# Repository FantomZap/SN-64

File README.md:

# SN 64

SN 64 is an active engineering project for an FPGA-based SNES/Super Famicom cartridge adapter. **The target is one adapter for both an original Nintendo 64 and ModRetro M64 through the standard N64 cartridge interface, without internal console modifications.** Compatibility has not yet been demonstrated on hardware.

The FPGA will recreate the SNES motherboard environment and provide a protected, complete SNES cartridge interface. Original SNES/SFC cartridges, Super EverDrive X5/X6, and FXPAK Pro are primary compatibility targets. The host console supplies controller input and runs the adapter's configuration and diagnostics bootstrap.

## Current status

**The project now includes a simulated SNES console candidate with a contention-checked physical cartridge bridge and a simulated N64/M64 host endpoint (reused SummerCart64 PI controller with an SN64 ROM window and mailbox), editable mechanical reference parts, and the KiCad cartridge/USB circuit draft. No completed or tested SN 64 hardware exists yet.** The [core evaluation](fpga/README.md) reuses pinned SNESTang sources and includes original diagnostics, synthesis and internal FPGA fit experiments. The [mechanical package](mechanical/README.md) contains FreeCAD, STEP and STL files for a socket hole-pattern coupon and source N64 board reference; these are not a final enclosure. The [editable schematic](hardware/sn64/README.md), revision `0.4-r3`, contains both cartridge connectors and five child sheets wired together by a shared net-name contract: the [USB programmer](hardware/sn64/usb-programmer.kicad_sch) (USB-C, protection, FT232HL, isolated JTAG), the [cartridge interface](hardware/sn64/cart-interface.kicad_sch) (5 V/3.3 V translators, reset/IRQ/CIC), the [FPGA](hardware/sn64/fpga.kicad_sch) (ECP5-85F with every ball assigned, configuration flash, N64 bus switches), [power](hardware/sn64/power.kicad_sch) (host/USB source selection, regulators, default-off cartridge power, monitors) and [clock/cartridge audio](hardware/sn64/av-clock.kicad_sch) (Si5351A, PCM1808 ADC). The FPGA design is routed on that sheet's real pinout.

Independent static checks on the integrated schematic: ERC 0 errors; 30 interface, 69 USB, 20 cartridge, 23 power, 30 clock/A-V and 4 root-connectivity checks pass; the FPGA sheet passes 12 of 13, and the failing check is a recorded open decision (a 5 V divider feeding one FPGA ball). These verify source agreement and schematic connectivity, not working hardware or USB compliance. The [136-entry requirements register](docs/requirements.md) preserves every specification target and records partial evidence separately from acceptance. Several footprints, the final BOM, board-level I/O timing, power and signal-integrity analysis, PCB layout, enclosure and every hardware test remain pending. **This is not fabrication ready.**

Every target in the original specification remains in scope, including PAL, protection, save integrity, telemetry, independent recovery, factory testing, and the additional requirements. The SNES picture and sound go to the console over the cartridge bus and appear on the console's own output (M64 HDMI, N64 AV jack); the adapter has no video output of its own. M64's reserved contacts stay isolated.

**v2 (branch `v2`, 2026-09-30):** a second board set that keeps every specification target and moves the clock generation, cartridge-audio ADC and rail telemetry into the FPGA, on one board that stands in the console's slot. 182 parts against 380, 17 chips against 47, FPGA signals on the outer three ball rings. The USB-C port is on the player's right and loads the board, blank or not, through a small loader chip on the FPGA's JTAG port ([USB loader](docs/design/usb-loader.md), 2026-10-02). Generated schematic (ERC 0 errors), simulated logic, scripted placement and autorouting. See [v2 board write-up](docs/design/v2-board.md); not fabrication-ready.

## Documents

- [Engineering specification, Rev A](SN_64_Engineering_Specification_Rev_A.docx)
- [Engineering implementation plan](docs/superpowers/plans/2026-09-28-sn64-engineering-plan.md)
- [Full requirements and acceptance register](docs/requirements.md)
- [System architecture and integration status](docs/architecture.md)
- [Console-core evaluation and reproducible builds](fpga/README.md)
- [Physical cartridge bridge design and open tests](docs/design/physical-cartridge-bridge.md)
- [Cartridge bridge implementation and simulation evidence](docs/design/cartridge-bridge-implementation.md)
- [N64/M64 endpoint implementation and mailbox map](docs/design/n64-endpoint-implementation.md)
- [N64 CIC lockout implementation](docs/design/n64-cic-implementation.md)
- [Power-control state machine](docs/design/power-sequencer-implementation.md)
- [Cartridge check: detecting a cartridge that is in back to front](docs/design/reversed-cartridge-detection.md)
- [Clock plan and region selection](docs/design/clock-plan.md)
- [Controller path and default N64 mapping](docs/design/controller-path-implementation.md)
- [SNES CIC lock and region detection](docs/design/snes-cic-implementation.md)
- [N64 bootstrap menu ROM](docs/design/n64-bootstrap.md)
- [Menu ideas: candidate features and a new layout (nothing decided)](docs/design/menu-ideas.md)
- [Integrated top level and system simulation](docs/design/system-integration.md)
- [Bootstrap ROM window from the configuration flash](docs/design/bootrom-flash.md)
- [Mechanical architecture: board arrangement, insertion depths, region-free opening](docs/design/mechanical-architecture.md)
- [Console video path: SNES picture and sound through the N64/M64's own output](docs/design/console-video-path.md)
- [Frame lock: one Super NES picture per console picture, compatibility mode, sound path](docs/design/frame-lock.md)
- [ROM-header region fallback](docs/design/header-region-probe.md)
- [On-board HDMI output (retired 2026-09-29)](docs/design/av-output-implementation.md)
- [Cartridge analog audio into the console stream](docs/design/cart-audio-implementation.md)
- [A real game through the simulated SN64](docs/design/game-simulation.md)
- [A game through the board's own wiring](docs/design/board-simulation.md)
- [Is the v2 board right? What has been checked, and what has not](docs/design/board-verification.md)
- [Pre-order review of the v2 board: what it found, the quote files, what only hardware can settle](docs/design/pre-order-review.md)
- [The USB loader chip: how a blank board gets its first load](docs/design/usb-loader.md)
- [Cartridge interface schematic sheet](docs/design/cart-interface-schematic.md)
- [FPGA schematic sheet and board pinout](docs/design/fpga-schematic.md)
- [Power schematic sheet](docs/design/power-schematic.md)
- [v2 board: schematic write-up, rationale, files](docs/design/v2-board.md)
- [Clock and cartridge-audio schematic sheet](docs/design/av-clock-schematic.md)
- [Cartridge data-bus source evidence and unresolved behavior](docs/design/bus-electrical-evidence.md)
- [FPGA/package, supply and board reuse review](docs/design/fpga-board-selection.md)
- [Power architecture, including M64 USB power](docs/design/power-architecture.md)
- [Socket selection and missing manufacturer dimensions](docs/design/socket-selection.md)
- [Editable mechanical references and fit coupon](mechanical/README.md)
- [Peripheral research and current decisions](docs/research/snes-peripherals.md)
- [Reusable SNES circuits, layouts and FPGA source](docs/research/reusable-designs.md)
- [Connector, cartridge and mounting dimensions](docs/dimensions.md)
- [Official M64 schematics and mechanical references](docs/research/m64-reference-files.md)
- [Local reference collection and source manifests](references/README.md)
- [KiCad cartridge-interface draft and verification](hardware/sn64/README.md)
- [SNES signal directions and electrical notes](docs/design/snes-interface-notes.md)
- [N64/M64 signal directions and power references](docs/design/n64-interface-notes.md)
- [sd2snes level-shifter reuse review](docs/design/translation-reuse-review.md)
- [USB programming architecture and remaining integration](docs/design/usb-programming-architecture.md)
- [USB connector mechanics and crystal selection](docs/design/usb-connector-mechanics.md)
- [Dated project work log](docs/project-work-log.md)

Current input decisions are standard, configurable N64-to-SNES controller mapping; no multitap; and undecided Super Scope/Justifier support. Virtual SNES mouse control using an N64 controller is deferred to a later FPGA/firmware update. The initial design must preserve the necessary input data, update path, and justified resource margins. Other researched accessories are candidates, not selected features.

**USB-C is mandatory in the first hardware revision.** Provide a side-mounted, externally accessible USB-C data port for initial firmware/FPGA programming, subsequent updates and recovery from a computer. It must be usable without a successful N64 or M64 boot. Include the connector, supporting programming circuitry and enclosure opening in the initial design; a power-only port or a future hardware addition does not satisfy this requirement. The bridge circuit is now drawn, but blank-board loading, persistent image programming and recovery still require the selected FPGA/storage, their power design, host software and bench validation.

## Tools and research approach

- **KiCad 10.0.6:** schematics, PCB layout, checks, and manufacturing exports.
- **FreeCAD 1.1.4:** dimensioned enclosure and mechanical assembly models.
- **Blender:** available for visualization and mesh work.
- **OSS CAD Suite 2026-09-28:** Yosys/Slang, Verilator, nextpnr-ecp5 and programming utilities; [pinned toolchain](fpga/reports/toolchain.json). Initial loading of actual SN64 hardware is still untested.

Start by adapting working upstream designs: reuse their HDL, circuits, layouts, footprints and mechanical CAD where they fit. The main custom work is integrating the physical SNES cartridge bridge with the SNES core, protected power, the N64 host endpoint, A/V and enclosure. Dimensions and interface assumptions retain their provenance and are cross-checked. Physical fit and functional tests follow adaptation.

## Planned outputs

These directories describe the intended outputs. Cartridge/USB schematics, the core candidate/tests, mechanical reference models and the acceptance register exist; the complete product implementations remain in progress.

| Planned directory | Contents |
|---|---|
| `references/` | Reference drawings, datasheets, CAD provenance, and license records |
| `hardware/sn64/` | KiCad schematic, PCB, libraries, and component models |
| `fpga/` | HDL, core integration, simulations, and constraints |
| `firmware/` | N64 bootstrap, controls, diagnostics, updates, and recovery |
| `mechanical/` | Enclosure CAD, drawings, fit samples, and assembly models |
| `test/` | Bring-up procedures, fixtures, measurements, and compatibility results |
| `manufacturing/` | Versioned PCBWay fabrication, assembly, and enclosure packages |

PCBWay is the intended manufacturing provider. Release deliverables include editable KiCad sources, schematic PDFs, Gerbers and NC drills, stack-up/fabrication notes, BOM with manufacturer part numbers and approved alternates, placement files, assembly drawings, programming/test instructions, and test-point/JTAG documentation. Enclosure deliverables include editable CAD, STEP/STL parts, dimensioned drawings, material/finish/fastener notes, and verified interface dimensions.

Manufacturing and compatibility claims will follow prototype bring-up, physical fit checks, and recorded validation on both hosts.

## Licensing

SN64 is open hardware and free software: [GPL-3.0-or-later](LICENSE-GPL-3.0-or-later.txt) for the FPGA logic, firmware and scripts, and [CERN-OHL-S-2.0](LICENSE-CERN-OHL-S-2.0.txt) for the hardware design files and documentation. [LICENSING.md](LICENSING.md) says what applies to what and what you may and must do; [NOTICE](NOTICE) holds the attribution terms. Credit line: **SN64 by FantomZap**, source at <https://github.com/FantomZap/SN-64>.

## Credits

SN64 is built on other people's open work, above all [SNESTang](https://github.com/nand2mario/snestang) by nand2mario (a port of the SNES core by srg320 and gyurco) and [SummerCart64](https://github.com/Polprzewodnikowy/SummerCart64) by Mateusz Faderewski. The full list, with what each project contributed and its licence, is in [CREDITS.md](CREDITS.md).

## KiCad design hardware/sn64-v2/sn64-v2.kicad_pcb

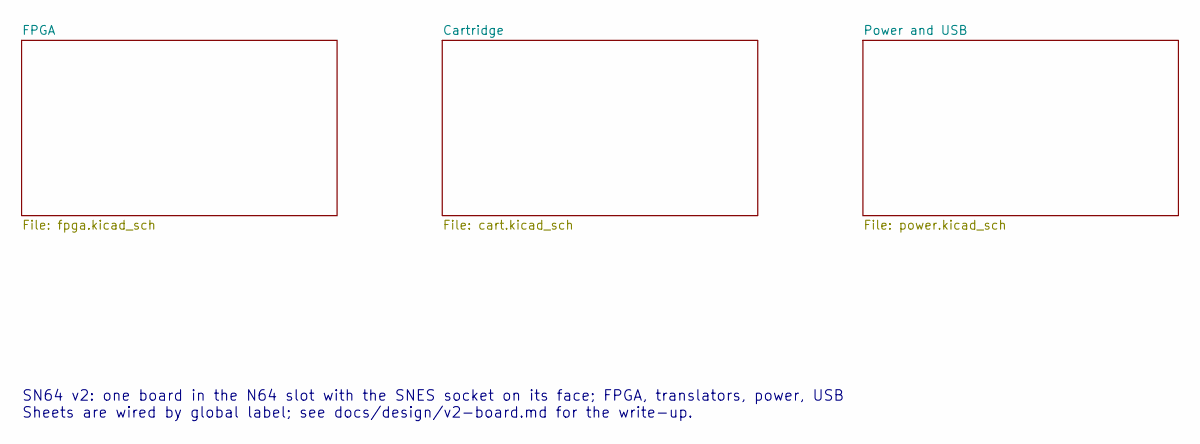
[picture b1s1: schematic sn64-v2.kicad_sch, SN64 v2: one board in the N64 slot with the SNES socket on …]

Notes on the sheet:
SN64 v2: one board in the N64 slot with the SNES socket on its face; FPGA, translators, power, USB Sheets are wired by global label; see docs/design/v2-board.md for the write-up.

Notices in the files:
hardware/sn64-v2/sn64-v2.kicad_pcb:
SN64 by FantomZap github.com/FantomZap/SN-64 CERN-OHL-S-2.0
